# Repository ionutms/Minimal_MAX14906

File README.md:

# Minimal_MAX14906

## Overview

This repository contains a minimal KiCad design project for the Analog Devices MAX14906, a quad-channel industrial digital I/O device. The project includes schematic designs and PCB layout files.

## Disclaimer

> [!NOTE]
> This project is provided "as is" and without any warranty, express or implied. For more details, please see the [LICENSE](LICENSE) file.

## About the MAX14906

The MAX14906 from Analog Devices is a quad-channel industrial digital input/output device for industrial control and automation applications. It is compliant with IEC 61131-2 standards.

Key features include:

- **Configurable Channels:** Each of the four channels can be independently configured as:
  - High-Side Switch
  - Push-Pull Driver
  - Digital Input (Type 1, 2, or 3)
- **Wide Operating Range:** 10V to 40V supply voltage range.
- **Robustness and Protection:** Features on-chip diagnostics like open-wire detection, thermal shutdown and undervoltage monitoring. It also features SafeDemag™ for safely turning off inductive loads.
- **Control Interface:** SPI interface for configuration and diagnostics.
- **Operating Temperature Range:** -40°C to +125°C.

## Project Structure

```
minimal_max14906/
├── minimal_max14906.kicad_sch       # Main schematic file
├── minimal_max14906.kicad_pcb       # PCB layout file
├── minimal_max14906.kicad_pro       # Project configuration file
├── fp-lib-table                     # Footprint library table
├── sym-lib-table                    # Symbol library table
├── project_jobs_set.kicad_jobset    # Project job settings
├── ibom.config.ini                  # Interactive BOM configuration
├── docs/                            # Documentation files
│   ├── pictures/                    # Images and photos
│   ├── schematics/                  # Schematic PDF exports
│   └── 3d_models/                   # 3D model files
└── KiCAD_Symbols_Generator/         # Submodule for symbol generation from CSV data
```

## Project Features

This design provides a minimal implementation of the MAX14906 with the following features:

- **Power Supply:**
  - VDD: +24V
  - VSS: 0V
  - VLOGIC: +3.3V
- **Channel Configuration:**
  - Basic protection circuits for each of the four I/O channels.
- **Bill of Materials (BOM):**
  - Interactive HTML BOM (`ibom.html`) for easy component identification and sourcing.
- **Libraries:**
  - Comprehensive symbol and footprint libraries integrated as a submodule.
- **3D Model:**
  - Includes a 3D model of the board for better visualization.

## Getting Started

### Prerequisites

- [KiCad EDA](https://www.kicad.org/) version 9.0 or later installed on your system
- Git (for cloning the repository and submodule management)

### Opening the Project

1. **Clone the repository** (including submodules):
   ```bash
   git clone --recursive https://github.com/ionutms/Minimal_MAX14906.git
   ```
   
   If you've already cloned the repository without submodules, initialize them with:
   ```bash
   git submodule init
   git submodule update
   ```

2. **Open the project in KiCad**:
   - Launch KiCad
   - Click "Open Existing Project"
   - Navigate to the cloned repository folder
   - Select the `minimal_max14906.kicad_pro` file

3. **Explore the design**:
   - Open the schematic editor to view the circuit design
   - Open the PCB editor to view the board layout
   - Review the symbol and footprint libraries used in the design

### Project Files

- **Main schematic**: `minimal_max14906.kicad_sch` - Contains the primary circuit design with the MAX14906 and support components
- **PCB layout**: `minimal_max14906.kicad_pcb` - Physical board design file with proper component placement
- **Project configuration**: `minimal_max14906.kicad_pro` - KiCad project settings

## Dependencies

This project has the following dependencies:

### 1. KiCAD Symbols Generator

This repository uses [KiCAD_Symbols_Generator](https://github.com/ionutms/KiCAD_Symbols_Generator) as a submodule for custom symbol generation.

To initialize the submodule after cloning this repository:

```bash
git submodule update --init --recursive
```

### 2. 3D Models

This project requires the [3D_Models_Vault](https://github.com/ionutms/3D_Models_Vault) repository for 3D models.

#### Setup for KiCAD 9:

1. Clone the 3D models repository:
   ```bash
   git clone https://github.com/ionutms/3D_Models_Vault.git
   ```

2. In KiCAD 9, add an environment variable:
   - Variable name: `KICAD9_3D_MODELS_VAULT`
   - Variable value: Full path to where you cloned the 3D_Models_Vault repository

## Usage

After setting up the dependencies, open the project in KiCad 9 to access all features including the 3D models.

## Symbol Generator Submodule

This project includes the KiCAD_Symbols_Generator as a submodule, which provides tools for generating KiCad symbols from CSV data files. For more information on using this tool, see the [KiCAD_Symbols_Generator documentation](minimal_max14906/KiCAD_Symbols_Generator/README.md).

## Documentation

The `docs` folder contains:
- Schematic PDF exports
- Images and photos of the design
- 3D model files (GLB and WRL formats)

## Visuals

The following images showcase the PCB design from different perspectives:

*Top View of the PCB*

*Side View of the PCB*

*Bottom View of the PCB*

## License

This project is licensed under the MIT License - see the [LICENSE](LICENSE) file for details.

## References

- [MAX14906 Datasheet](https://www.analog.com/en/products/max14906.html)
- [KiCad EDA](https://www.kicad.org/)

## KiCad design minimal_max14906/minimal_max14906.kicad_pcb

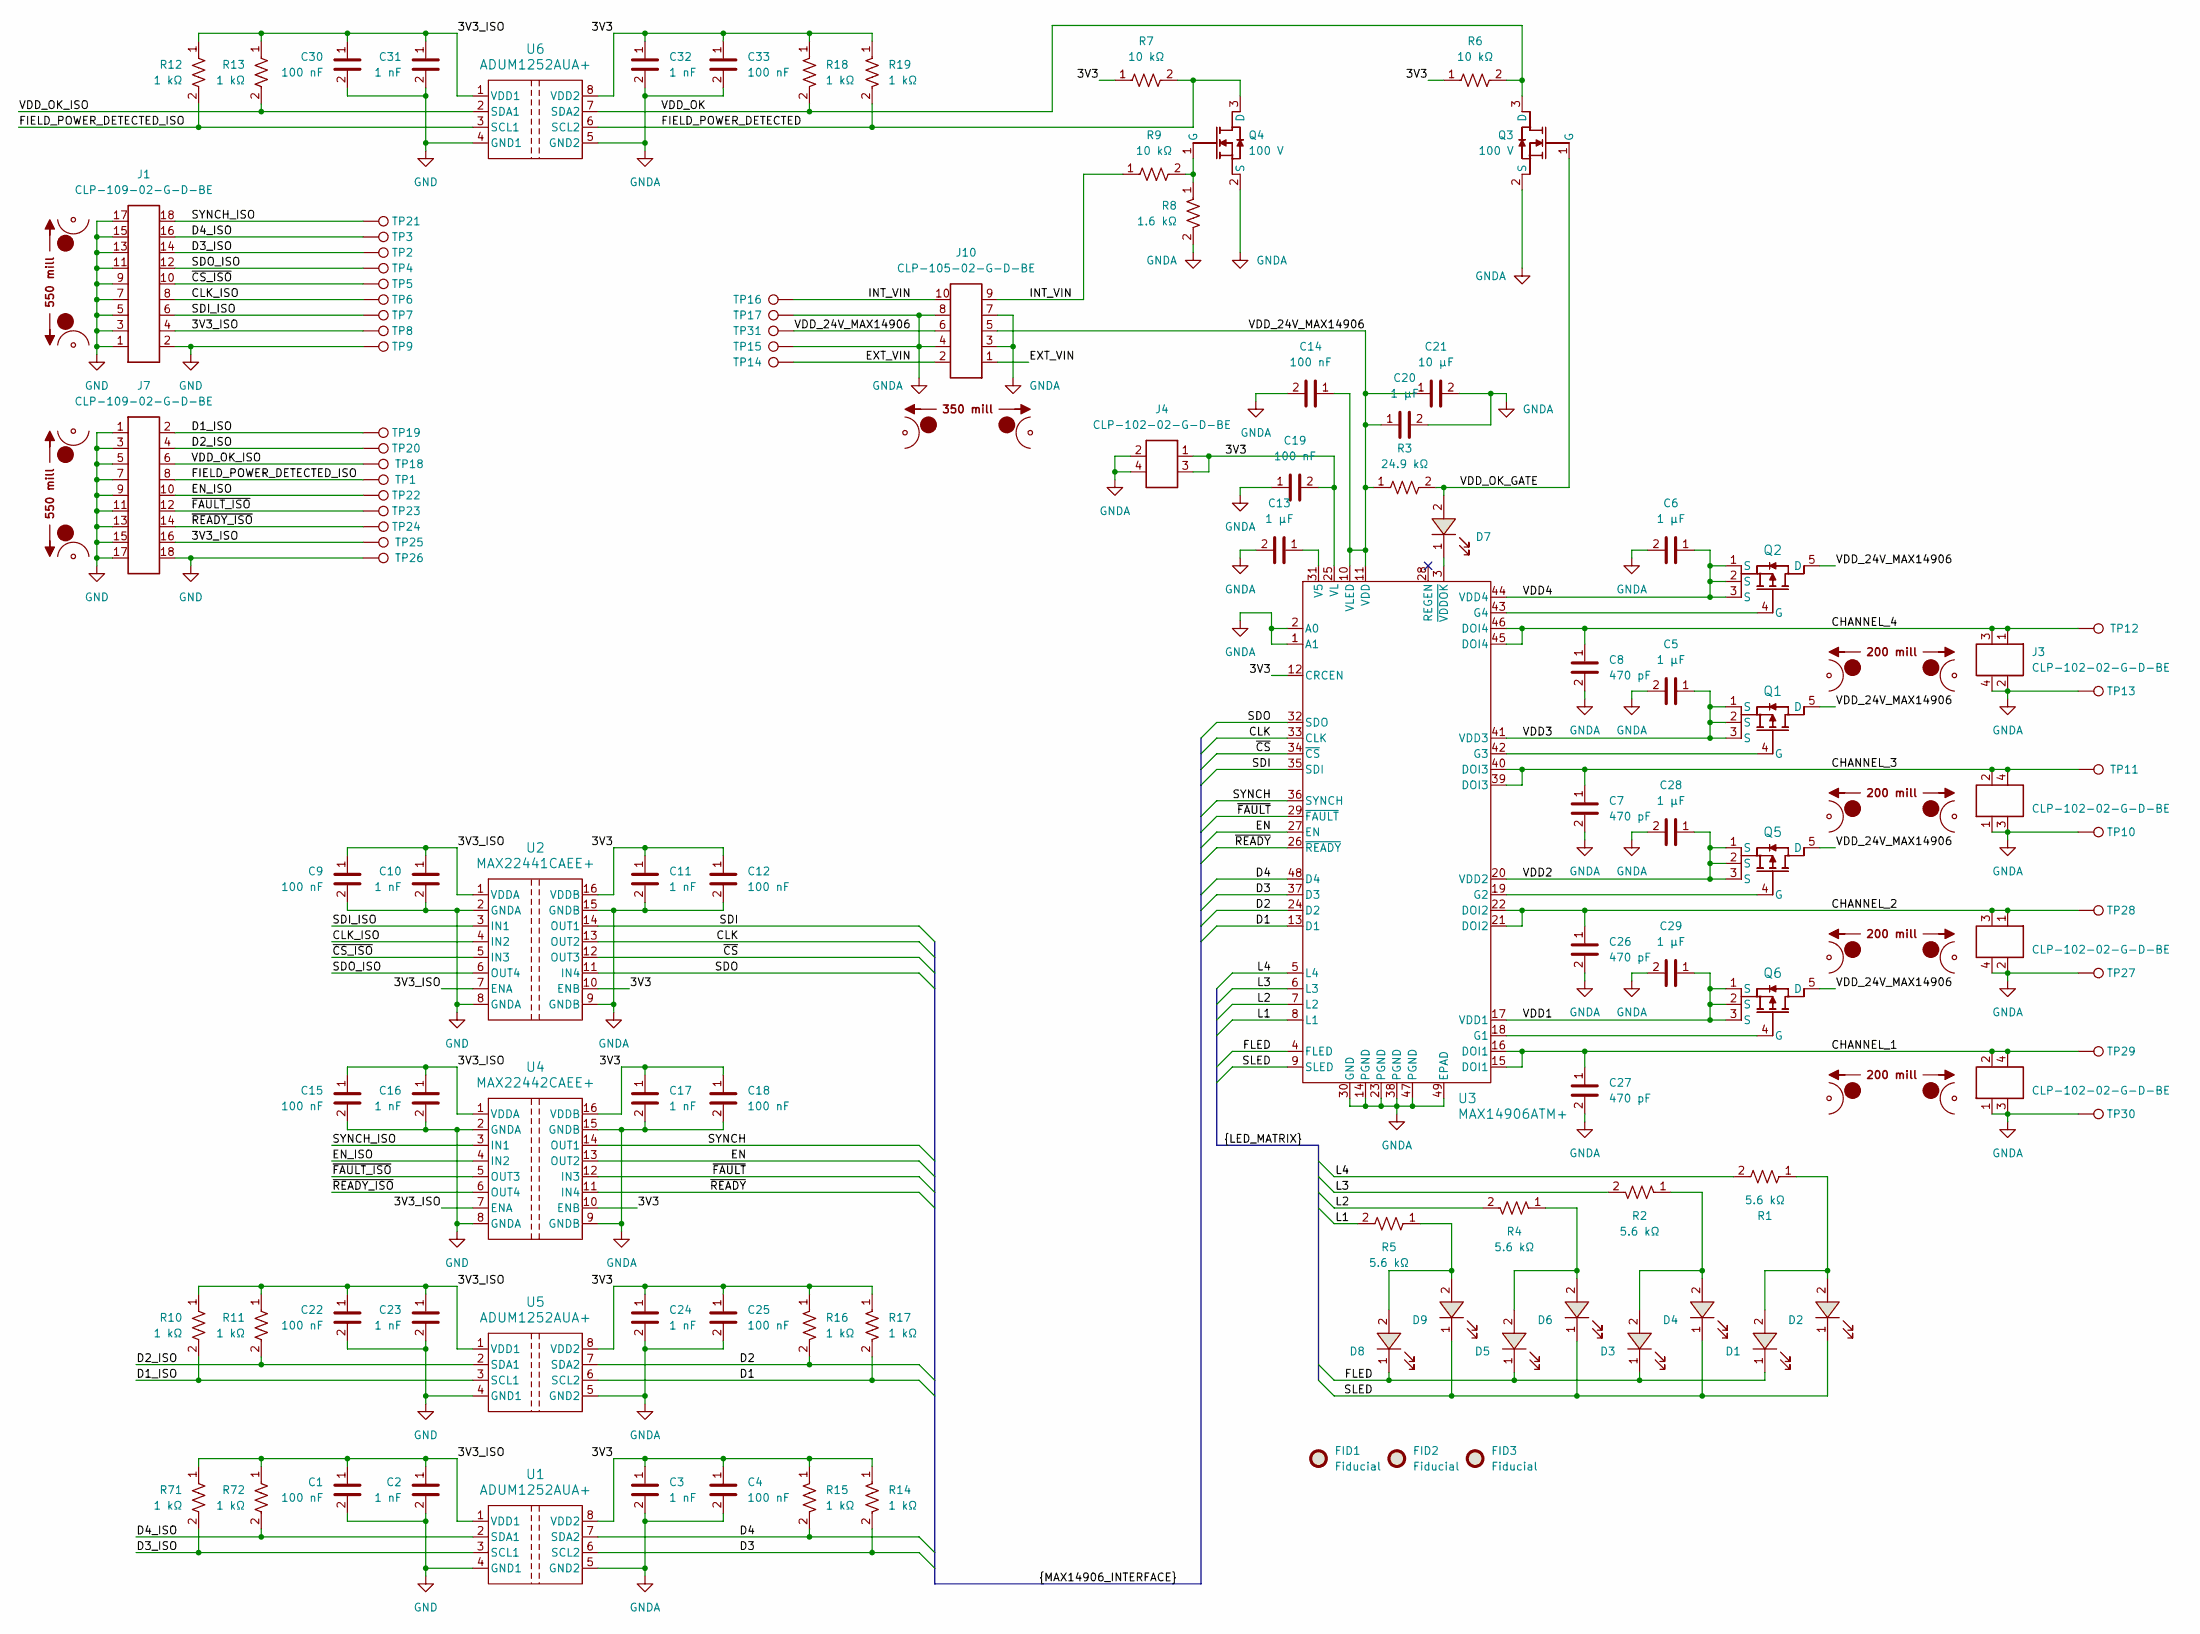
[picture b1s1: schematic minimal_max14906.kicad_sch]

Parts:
C1, C4, C9, C12, C14, C15, C18, C19, C22, C25, C30, C33: 100 nF; C_0402_1005Metric; Voltage Rating DC 50 VDC; Tolerance 10%; MPN GCM155R71H104KE02D
C2, C3, C10, C11, C16, C17, C23, C24, C31, C32: 1 nF; C_0402_1005Metric; Tolerance 10%; Voltage Rating 50V; MPN GCM155R71H102KA37D
C5, C6, C20, C28, C29: 1 µF; C_0805_2012Metric; Voltage Rating DC 100 VDC; Tolerance 10%; MPN GRJ21BC72A105KE11L
C7, C8, C26, C27: 470 pF; C_0603_1608Metric; Voltage Rating DC 100 VDC; Tolerance 10%; MPN VJ0603Y471KXBAC
C13: 1 µF; C_0402_1005Metric; Voltage Rating DC 16 VDC; Tolerance 10%; MPN C1005X6S1C105K050BC
C21: 10 µF; C_1206_3216Metric; Voltage Rating DC 50 VDC; Tolerance 10%; MPN CL31B106KBHNNN#
D1, D3, D5, D8: 1.8 V; LED_RED_0402_1005Metric; MPN APHHS1005LSECK/J3-PF
D2, D4, D6, D7, D9: 1.8 V; LED_GREEN_0402_1005Metric; MPN APHHS1005CGCK
FID1, FID2, FID3: Fiducial; Fiducial_0.5mm_Mask1mm
J1, J7: CLP-109-02-G-D-BE; Current Rating (A) 5.2; Voltage Rating (V) 300; MPN CLP-109-02-G-D-BE
J2, J3, J4, J8, J9: CLP-102-02-G-D-BE; Current Rating (A) 5.2; Voltage Rating (V) 300; MPN CLP-102-02-G-D-BE
J10: CLP-105-02-G-D-BE; Current Rating (A) 5.2; Voltage Rating (V) 300; MPN CLP-105-02-G-D-BE
MB1, MB6: mouse-bite-50mil-550mil
MB2, MB3, MB7, MB8: mouse-bite-50mil-200mil
MB4: mouse-bite-50mil-300mil; mouse-bite-50mil-350mil
Q1, Q2, Q5, Q6: -60.0 V; PowerPAK 1212-8; MPN SI7309DN-T1-GE3
Q3, Q4: 100 V; SOT-323; MPN BSS123WQ-7-F
R1, R2, R4, R5: 5.6 kΩ; R_0402_1005Metric; Voltage Rating 50V; Tolerance 5%; MPN RMCF0402JT5K60
R3: 24.9 kΩ; R_0402_1005Metric; Voltage Rating 50V; Tolerance 1%; MPN ERJ-2RKF2492X
R6, R7, R9: 10 kΩ; R_0402_1005Metric; Tolerance 1%; Voltage Rating 50V; MPN ERJ-2RKF1002X
R8: 1.6 kΩ; R_0402_1005Metric; Tolerance 1%; Voltage Rating 50V; MPN ERJ-2RKF1601X
R10, R11, R12, R13, R14, R15, R16, R17, R18, R19, R71, R72: 1 kΩ; R_0402_1005Metric; Tolerance 1%; Voltage Rating 50V; MPN ERJ-2RKF1001X
TP1, TP2, TP3, TP4, TP5, TP6, TP7, TP8, TP9, TP10, TP11, TP12, TP13, TP14, TP15, TP16, TP17, TP18, TP19, TP20, TP21, TP22, TP23, TP24, TP25, TP26, TP27, TP28, TP29, TP30, TP31: TestPoint; TestPoint_THTPad_Castelated
U1, U5, U6: ADUM1252AUA+; 21-0036_ADI; MPN ADUM1252AUA+
U2: MAX22441CAEE+; 21-0055_E16MS&plus_1F_ADI; MPN MAX22441CAEE+
U3: MAX14906ATM+; 21-0144H_T4877-6; MPN MAX14906ATM+
U4: MAX22442CAEE+; 21-0055_E16MS&plus_1F_ADI; MPN MAX22442CAEE+

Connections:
/3V3: C3.1, C4.1, C11.1, C12.1, C17.1, C18.1, C19.2, C24.1, C25.1, C32.1, C33.1, J4.1, J4.3, R6.1, R7.1, R14.1, R15.1, R16.1, R17.1, R18.1, R19.1, U1.8 (VDD2), U2.10 (ENB), U2.16 (VDDB), U3.12 (CRCEN), U3.25 (VL), U4.10 (ENB), U4.16 (VDDB), U5.8 (VDD2), U6.8 (VDD2)
/3V3_ISO: C1.1, C2.1, C9.1, C10.1, C15.1, C16.1, C22.1, C23.1, C30.1, C31.1, J1.4, J7.16, R10.1, R11.1, R12.1, R13.1, R71.1, R72.1, TP8.1, TP25.1, U1.1 (VDD1), U2.1 (VDDA), U2.7 (ENA), U4.1 (VDDA), U4.7 (ENA), U5.1 (VDD1), U6.1 (VDD1)
/CHANNEL_1: C27.1, J9.2, J9.4, TP29.1, U3.15 (DOI1), U3.16 (DOI1)
/CHANNEL_2: C26.1, J8.1, J8.3, TP28.1, U3.21 (DOI2), U3.22 (DOI2)
/CHANNEL_3: C7.1, J2.2, J2.4, TP11.1, U3.39 (DOI3), U3.40 (DOI3)
/CHANNEL_4: C8.1, J3.1, J3.3, TP12.1, U3.45 (DOI4), U3.46 (DOI4)
/CLK: U2.13 (OUT2), U3.33 (CLK)
/CLK_ISO: J1.8, TP6.1, U2.4 (IN2)
/D1: R17.2, U3.13 (D1), U5.6 (SCL2)
/D1_ISO: J7.2, R10.2, TP19.1, U5.3 (SCL1)
/D2: R16.2, U3.24 (D2), U5.7 (SDA2)
/D2_ISO: J7.4, R11.2, TP20.1, U5.2 (SDA1)
/D3: R14.2, U1.6 (SCL2), U3.37 (D3)
/D3_ISO: J1.14, R71.2, TP2.1, U1.3 (SCL1)
/D4: R15.2, U1.7 (SDA2), U3.48 (D4)
/D4_ISO: J1.16, R72.2, TP3.1, U1.2 (SDA1)
/EN: U3.27 (EN), U4.13 (OUT2)
/EN_ISO: J7.10, TP22.1, U4.4 (IN2)
/EXT_VIN: J10.1, J10.2, TP14.1
/FIELD_POWER_DETECTED: Q4.3 (D), R7.2, R19.2, U6.6 (SCL2)
/FIELD_POWER_DETECTED_ISO: J7.8, R12.2, TP1.1, U6.3 (SCL1)
/FLED: D1.1, D3.1, D5.1, D8.1, U3.4 (FLED)
/INT_VIN: J10.9, J10.10, R9.1, TP16.1
/L1: R5.2, U3.8 (L1)
/L2: R4.2, U3.7 (L2)
/L3: R2.2, U3.6 (L3)
/L4: R1.2, U3.5 (L4)
/SDI: U2.14 (OUT1), U3.35 (SDI)
/SDI_ISO: J1.6, TP7.1, U2.3 (IN1)
/SDO: U2.11 (IN4), U3.32 (SDO)
/SDO_ISO: J1.12, TP4.1, U2.6 (OUT4)
/SLED: D2.1, D4.1, D6.1, D9.1, U3.9 (SLED)
/SYNCH: U3.36 (SYNCH), U4.14 (OUT1)
/SYNCH_ISO: J1.18, TP21.1, U4.3 (IN1)
/VDD1: C29.1, Q6.1 (S), Q6.2 (S), Q6.3 (S), U3.17 (VDD1)
/VDD2: C28.1, Q5.1 (S), Q5.2 (S), Q5.3 (S), U3.20 (VDD2)
/VDD3: C5.1, Q1.1 (S), Q1.2 (S), Q1.3 (S), U3.41 (VDD3)
/VDD4: C6.1, Q2.1 (S), Q2.2 (S), Q2.3 (S), U3.44 (VDD4)
/VDD_24V_MAX14906: C14.1, C20.1, C21.1, J10.5, J10.6, Q1.5 (D), Q2.5 (D), Q5.5 (D), Q6.5 (D), R3.1, TP31.1, U3.10 (VLED), U3.11 (VDD)
/VDD_OK: Q3.3 (D), R6.2, R18.2, U6.7 (SDA2)
/VDD_OK_GATE: D7.2, Q3.1 (G), R3.2
/VDD_OK_ISO: J7.6, R13.2, TP18.1, U6.2 (SDA1)
/~CS_ISO: J1.10, TP5.1, U2.5 (IN3)
/~CS: U2.12 (OUT3), U3.34 (~CS)
/~FAULT_ISO: J7.12, TP23.1, U4.5 (OUT3)
/~FAULT: U3.29 (~FAULT), U4.12 (IN3)
/~READY_ISO: J7.14, TP24.1, U4.6 (OUT4)
/~READY: U3.26 (~READY), U4.11 (IN4)
GND: C1.2, C2.2, C9.2, C10.2, C15.2, C16.2, C22.2, C23.2, C30.2, C31.2, J1.1, J1.2, J1.3, J1.5, J1.7, J1.9, J1.11, J1.13, J1.15, J1.17, J7.1, J7.3, J7.5, J7.7, J7.9, J7.11, J7.13, J7.15, J7.17, J7.18, TP9.1, TP26.1, U1.4 (GND1), U2.2 (GNDA), U2.8 (GNDA), U4.2 (GNDA), U4.8 (GNDA), U5.4 (GND1), U6.4 (GND1)
GNDA: C3.2, C4.2, C5.2, C6.2, C7.2, C8.2, C11.2, C12.2, C13.2, C14.2, C17.2, C18.2, C19.1, C20.2, C21.2, C24.2, C25.2, C26.2, C27.2, C28.2, C29.2, C32.2, C33.2, J2.1, J2.3, J3.2, J3.4, J4.2, J4.4, J8.2, J8.4, J9.1, J9.3, J10.3, J10.4, J10.7, J10.8, Q3.2 (S), Q4.2 (S), R8.2, TP10.1, TP13.1, TP15.1, TP17.1, TP27.1, TP30.1, U1.5 (GND2), U2.9 (GNDB), U2.15 (GNDB), U3.1 (A1), U3.2 (A0), U3.14 (PGND), U3.23 (PGND), U3.30 (GND), U3.38 (PGND), U3.47 (PGND), U3.49 (EPAD), U4.9 (GNDB), U4.15 (GNDB), U5.5 (GND2), U6.5 (GND2)
unnamed: D1.2, D2.2, R1.1
unnamed: D3.2, D4.2, R2.1
unnamed: D5.2, D6.2, R4.1
unnamed: D8.2, D9.2, R5.1
unnamed: Q1.4 (G), U3.42 (G3)
unnamed: Q2.4 (G), U3.43 (G4)
unnamed: Q4.1 (G), R8.1, R9.2
unnamed: Q5.4 (G), U3.19 (G2)
unnamed: Q6.4 (G), U3.18 (G1)
unnamed: C13.1, U3.31 (V5)
unnamed: D7.1, U3.3 (~VDDOK)

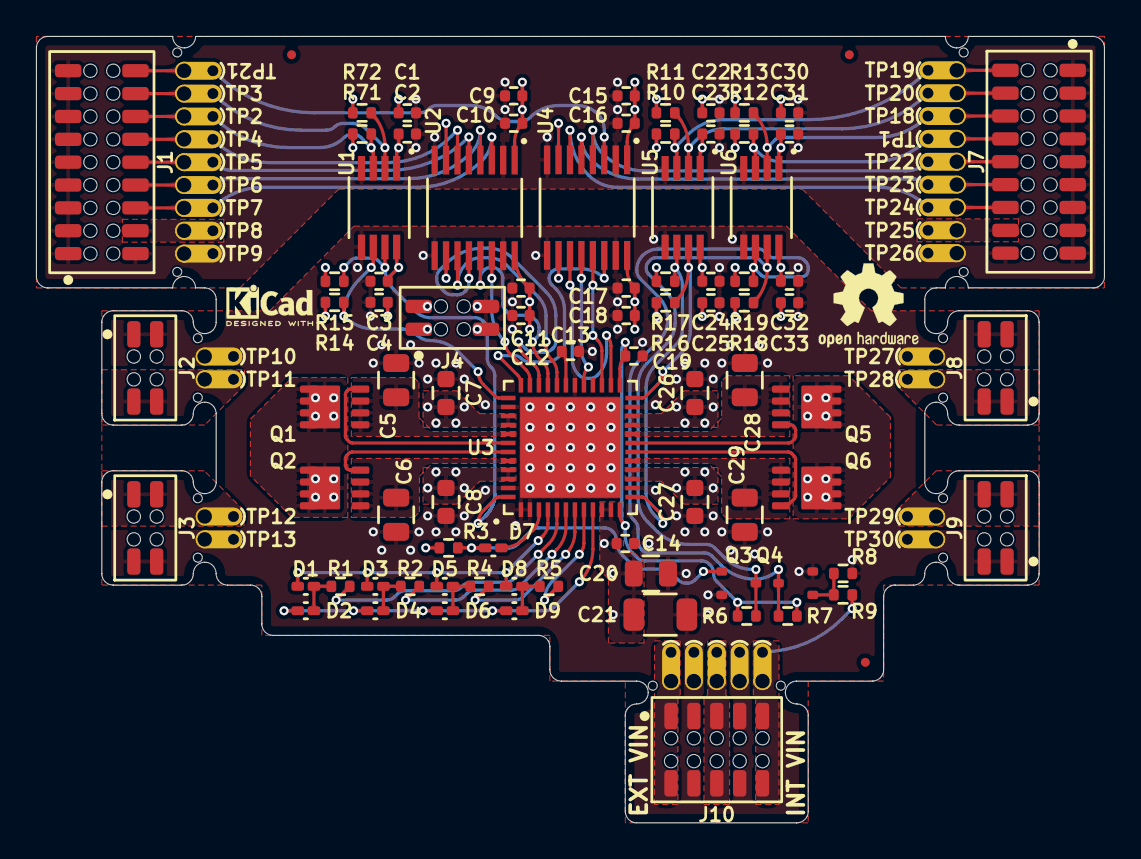
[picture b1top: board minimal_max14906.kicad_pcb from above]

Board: 4 copper layers, 59.3 x 43.7 mm, 124 parts (0 on the bottom side), 61 nets.

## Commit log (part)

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2025-01-28 Update subproject commit for KiCAD Symbol Generator
2025-01-29 Update VRML file reference in KiCAD project
2025-01-29 Minor updates to project files
2025-01-31 Update KiCAD Symbol Generator subproject commit and adjust pad dimensions
2025-01-31 Backup
2025-02-03 Minor updates
2025-02-03 Minor updates to improve project consistency
2025-02-05 Minor updates for project consistency
2025-02-05 Update KiCAD Symbol Generator subproject commit
2025-02-07 Update KiCAD Symbol Generator and configuration files
2025-02-08 Add GLB 3D model
2025-03-01 Update KiCAD Symbol Generator subproject and add new footprints for fiducial markers
2025-03-02 Update KiCAD Symbol Generator with new features and improvements
2025-03-02 Update KiCAD schematic references for consistency and accuracy
2025-03-10 Update KiCAD Symbol Generator subproject reference and minimal_max14906.glb file
2025-03-10 Update KiCAD schematic references for improved clarity and consistency
2025-03-10 Update minimal_max14906.glb with latest changes
2025-03-15 Update KiCAD Symbol Generator subproject reference
2025-03-16 Remove KiCAD Symbol Generator submodule reference
2025-03-16 Add KiCAD Symbols Generator submodule reference
2025-03-16 Update KiCAD Symbols Generator submodule and adjust library paths in fp-lib-table
2025-03-18 Update KiCAD Symbols Generator submodule to latest commit
2025-03-18 Switch to KiCad 9
2025-03-19 Add .log files to .gitignore
2025-03-19 Add project job set configuration for minimal_max14906
2025-03-19 Update project job set configuration for minimal_max14906 to enable via cutting, filling vias, shape fusion, and overwrite options
2025-03-19 Update minimal_max14906 project files with new side image and update .glb file
2025-03-19 Enable drill origin usage in project job set configuration for minimal_max14906
2025-03-19 Update minimal_max14906 side image file
2025-03-19 Refactor project job set configuration for minimal_max14906 to update export command and output settings
2025-03-19 Update minimal_max14906 .glb and side image files
2025-03-20 Add new special_execute command for rendering top PCB image in project job set configuration
2025-03-20 Update subproject commit for KiCAD Symbols Generator
2025-03-20 Add top image and update file references for minimal_max14906
2025-03-21 Update project job set configuration for minimal_max14906 to specify output paths and filenames for GLB, WRL, and PNG exports
2025-03-21 Remove obsolete top and side images; add new GLB and updated picture files for minimal_max14906
2025-03-22 Update README.md to include project dependencies and setup instructions for KiCAD and 3D models
2025-03-24 Add switches footprints and symbols to KiCAD library tables
2025-03-24 Update pad dimensions and add net colors for minimal_max14906
2025-03-24 Update 3D models and images for minimal_max14906
2025-04-04 Add schematic export job and output folder for PDF generation
2025-04-04 development backup
2025-04-04 Add schematic PDF for minimal_max14906
2025-04-04 Update 3D models and images for minimal_max14906 documentation
2025-04-05 Update schematic PDF for minimal_max14906 with formatting adjustments and corrections
2025-04-05 Update minimal_max14906 documentation and schematic PDF formatting
2025-04-05 Update minimal_max14906 documentation and schematic PDF
2025-04-08 Update minimal_max14906 schematic PDF for formatting improvements
2025-04-08 Update minimal_max14906 schematic PDF
2025-04-18 Update KiCad documentation (schematics and PCB renders)
2025-04-18 Add configuration file for default zoom factor and update workflow to use it
2025-04-18 Update PDF export command to use 'gruvbox' theme for schematic generation
2025-04-18 Update PDF export command to include 'gruvbox' theme for schematic generation
2025-04-19 dev backup
2025-04-19 Add Gruvbox theme support for KiCad PDF exports
2025-04-20 Refactor KiCad job to generate schematic PDF and PCB render on the same step
2025-04-20 Update KiCad configuration and workflow to use project zoom factor for top view rendering
2025-04-20 Fix formatting in KiCad job for PCB render command
2025-04-20 Fix quotes in PCB render command options for consistency
2025-04-20 Refactor KiCad job to streamline PCB rendering steps and improve directory management
2025-04-20 Fix formatting in PCB render command options for consistency
2025-04-20 Fix quotes in KiCad configuration for project rotation coordinates
2025-04-20 Fix quotes in PCB render command options for rotate parameter
2025-04-20 Fix rotation parameter in PCB render command for consistency
2025-04-20 Update rotation coordinates in KiCad configuration to default values
2025-04-20 Update rotation coordinates in KiCad configuration to 0,0,45
2025-04-20 Update rotation coordinates in KiCad configuration to -45
2025-04-20 Update rotation coordinates in KiCad configuration to 45,0,45
2025-04-20 Update rotation coordinates in KiCad configuration to -45,0,45
2025-04-20 Fix escape character in rotation coordinates in KiCad configuration
2025-04-20 Fix rotation coordinates formatting in KiCad configuration and workflow
2025-04-20 Fix rotation coordinates syntax in KiCad output generation
2025-04-20 Fix rotation coordinates extraction and export in KiCad workflow
2025-04-20 Fix handling of custom rotation coordinates in KiCad workflow
2025-04-20 Refactor KiCad workflow to standardize zoom factor extraction and remove unused rotation coordinates
2025-04-20 Remove Gruvbox theme setup and PDF generation steps from KiCad workflow
2025-04-20 Update zoom factor for PCB render generation in workflow
2025-04-20 Add rotation option to PCB render generation in workflow
2025-04-20 Update PCB render generation to use default zoom factor from configuration
2025-04-20 Add default rotate factor to configuration and update workflow to use it
2025-04-20 Update PCB render generation to use fixed rotation angles
2025-04-20 Update PCB render generation to use dynamic rotation factor from configuration
2025-04-20 Update workflow to improve configuration loading for KiCad documentation generation
2025-04-20 Fix rotation factor variable usage in PCB render generation
2025-04-20 Fix formatting of rotate factor in configuration and update workflow to use correct variable syntax
2025-04-20 Remove default rotate factor from configuration and update workflow to eliminate unused variable
2025-04-20 Enhance KiCad job workflow to support custom zoom factor from configuration
2025-04-20 Rename PCB rendering step and update zoom factor for improved output quality
2025-04-20 Fix formatting in PCB rendering command for consistent rotation parameters
2025-04-20 Update GitHub Actions workflow for improved documentation generation
2025-04-20 Fix quoting in PCB rendering command for proper argument handling
2025-04-20 Fix PCB rendering command to handle errors gracefully and improve rotation parameter formatting
2025-04-20 Fix PCB rendering command to use zoom factor from configuration and update output file naming
2025-04-20 Refactor PCB rendering step to use jobset command and remove commented-out code
2025-04-20 Enhance PCB rendering step to restore functionality and utilize zoom factor from configuration
2025-04-20 Fix PCB rendering command to correctly apply zoom factor and adjust rotation parameters
2025-04-20 Update PCB rendering command to use variables for rotation and pan parameters
2025-04-20 Refactor PCB rendering command to use double quotes for rotation parameters and remove unused pan variable
2025-04-20 Comment out PDF schematic generation step and adjust PCB rendering command for rotation parameter
2025-04-20 Fix PCB rendering command to properly format rotation parameter
2025-04-20 Refactor PDF schematic generation and PCB rendering commands for improved clarity and maintainability
2025-04-20 Refactor PCB rendering command to streamline Docker execution and improve script clarity
2025-04-20 Fix rotation parameter syntax in PCB rendering command
2025-04-20 Refactor PCB 3D rendering command to streamline environment setup and remove unnecessary test step
2025-04-20 Set output filename for schematic export log
2025-04-20 update schematics
2025-04-20 update 3d models and images
2025-04-20 Refactor zoom factor handling in KiCad job configuration
2025-04-20 Remove merge conflict markers and clean up PCB rendering command in KiCad job workflow
2025-04-20 Refactor zoom factor handling in KiCad job configuration to ensure default values are used when configuration file is absent
2025-04-21 Add continuation to PCB rendering command for improved readability
2025-04-21 Update PCB rendering rotation parameters for improved output quality
2025-04-21 Fix zoom factor extraction and improve PCB rendering command output
2025-04-21 Update default zoom factor and adjust PCB rendering command parameters for improved output
2025-04-21 Fix default zoom factor assignment in KiCad job configuration
2025-04-21 Fix zoom factor extraction to properly parse value from configuration file
2025-04-21 Fix output path for KiCad 3D models in rendering step
2025-04-21 Add pan option to rendering command for improved output positioning
2025-04-21 Refactor zoom factor handling in KiCad job workflow
2025-04-21 Update zoom factor handling in KiCad job workflow to use side view zoom factor from configuration
2025-04-21 Refactor zoom factor extraction in KiCad job workflow to improve variable naming
2025-04-21 Remove debug output steps for directory permissions in KiCad job workflow
2025-04-21 Enhance KiCad job workflow with Docker caching and improved output generation
2025-04-21 Enhance Docker caching and cleanup in KiCad job workflow
2025-04-21 Enhance PCB rendering in KiCad job workflow with top and side view generation
2025-04-21 Update KiCad configuration and job workflow to include top view zoom factor
2025-04-21 Fix indentation in KiCad configuration for side view pan setting
2025-04-21 Update top view zoom factor in KiCad configuration
2025-04-21 Update side view zoom factor and pan settings in KiCad configuration
2025-04-21 Refactor GitHub Actions workflow by removing Docker Buildx setup and cache management steps
2025-04-21 Update KiCad documentation workflow to create project-specific directories and adjust file paths
2025-04-21 Remove unused images and schematic files for MAX14906 project
2025-04-21 Update KiCad documentation for minimal_max14906 (schematics and PCB renders)
2025-04-21 Fix output filename for KiCad schematic PDF generation
2025-04-21 cleanup
2025-04-21 Update 3D model for minimal_max14906
2025-04-21 Update minimal_max14906 3D model file
2025-04-21 Remove obsolete GLB file for minimal_max14906 3D model
2025-04-21 Enhance GitHub Actions workflow to determine and checkout default branch, clean output directories, and streamline push operations
2025-04-21 Add WRL file generation for PCB in KiCad workflow
2025-04-21 Fix casing for 3D model directories in KiCad documentation generation
2025-04-21 test
2025-04-21 Remove GLB and WRL file generation from KiCad documentation workflow
2025-04-21 update 3d models
2025-04-24 Update GitHub Actions workflow for KiCad documentation generation
2025-04-26 Adjust KiCad configuration parameters for improved view settings
2025-04-26 Adjust KiCad configuration parameters for top and side view settings
2025-05-23 Add cleanup step for old 3D model artifacts in GitHub Actions workflow
2025-05-23 Enhance 3D model export by including tracks, pads, zones, silkscreen, and soldermask
2025-05-23 Add --subst-models option to 3D model export commands in workflow
2025-05-24 Update trigger branch for 3D models generation workflow to 'doc_workflow'
2025-08-18 Add bottom view rendering support and fix file naming
2025-08-22 Update KiCad workflow files for 3D models and jobs generation
2025-08-28 Update KiCad Docker image version and enhance workflow capabilities
2025-09-02 Update README.md with comprehensive project documentation
2025-10-05 chore: update workflows from central repository
2025-10-05 chore: update workflows and kicad config from central repository
